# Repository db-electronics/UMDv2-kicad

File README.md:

# UMDv2
The Universal Mega Dumper v2 project aims to be a complete open-sourced solution for cartridge dumping and writing. It includes a very performant MCU which has a direct memory connection to a generalized databus consisting of 24 address bits and 16 data lines. Along with a dozen or so control signals, it should be sufficient to interface with most cartridge types.

## Cartridge Adapters
The UMDv2 by itself only includes a generalized connector with all its interfacing signals. Cartridge adapters must be used in order to interface to the physical media. All cartridge adapters, as they are created, are added to this project as submodules and will be linked in the CartAdapters directory.

### Cartridge Adapter ID
Each cartridge adapter has an MCP23008 on the I2C bus which identifies the console type for the adapter and thus prevents contention on IO.

* 0x00: no adapter
* 0x01: Sega Genesis 
* 0x02: Sega Master System

# Dependencies
## Parts Libraries
All components in this project depend on my KiCad libraries which are available at https://github.com/db-electronics/kicadlib . I don't use any pre-existing libraries - fight me.

## Firmware
There are two firmware components associated with this PCB: the STM32 fimware and the PC-side client. Both are available here:

* https://github.com/db-electronics/UMDv2-stm32
* https://github.com/db-electronics/UMDv2-python

Please note that version 2.0 is in its absolute infancy, don't expect to find any working releases in the firmware links above for the time being. The links are for provided provideness for completeness of documentation.

# Releases
## 2.0
https://oshpark.com/shared_projects/2dKXBoCG

The PCB version 2.0 release files are available in the releases section https://github.com/db-electronics/UMDv2-kicad/releases. Please note that this PCB is as of yet untested. Build at your own risk. I will post updates when I have begun testing this latest release.

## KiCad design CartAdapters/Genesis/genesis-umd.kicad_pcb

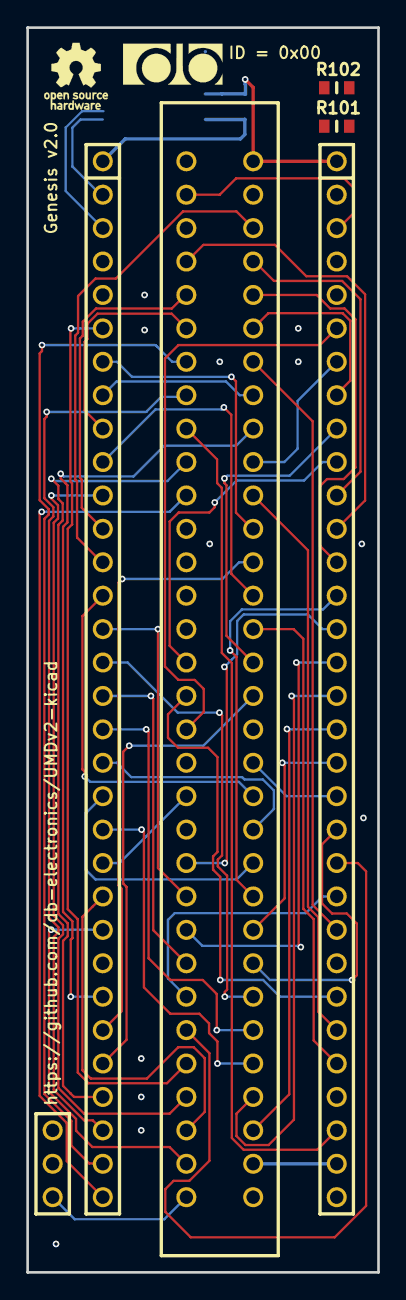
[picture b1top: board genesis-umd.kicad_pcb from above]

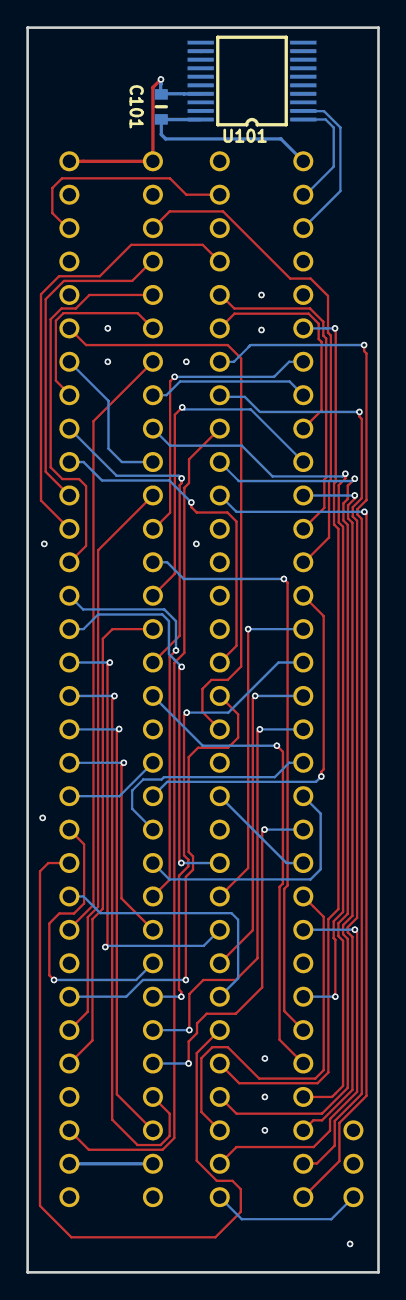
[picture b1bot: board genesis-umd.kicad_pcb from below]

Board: 2 copper layers, 26.7 x 94.6 mm, 6 parts (2 on the bottom side), 58 nets.

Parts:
C101: 0.1uF/50V; 0603
CON101: UMDv2-CONN; UMD-CONN-DIP64
CON102: GENESIS-CONN
R101, R102: 0; 0603
U101: MCP23008T-E_SS; SSOP-20

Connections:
+3V3: C101.1, CON101.1, U101.20
/5V_0: CON101.63, R101.2
/5V_1: CON101.34, CON102.A31
/A1: CON101.28, CON102.A17
/A2: CON101.37, CON102.A15
/A3: CON101.27, CON102.A13
/A4: CON101.38, CON102.A11
/A5: CON101.26, CON102.A9
/A6: CON101.41, CON102.A7
/A7: CON101.52, CON102.A5
/A8: CON101.13, CON102.A3
/A9: CON101.53, CON102.B4
/A10: CON101.12, CON102.B5
/A11: CON101.54, CON102.A4
/A12: CON101.57, CON102.A6
/A13: CON101.8, CON102.A8
/A14: CON101.58, CON102.A10
/A15: CON101.7, CON102.A12
/A16: CON101.10, CON102.A14
/A17: CON101.56, CON102.A16
/A18: CON101.9, CON102.B6
/A19: CON101.31, CON102.B7
/A20: CON101.30, CON102.B8
/A21: CON101.35, CON102.B9
/A22: CON101.29, CON102.B10
/A23: CON101.32, CON102.B11
/D0: CON101.14, CON102.A20
/D1: CON101.51, CON102.A23
/D2: CON101.16, CON102.A26
/D3: CON101.48, CON102.A29
/D4: CON101.21, CON102.A28
/D5: CON101.44, CON102.A25
/D6: CON101.20, CON102.A22
/D7: CON101.45, CON102.A19
/D8: CON101.19, CON102.A21
/D9: CON101.46, CON102.A24
/D10: CON101.18, CON102.A27
/D11: CON101.47, CON102.A30
/D12: CON101.17, CON102.B25
/D13: CON101.49, CON102.B24
/D14: CON101.15, CON102.B23
/D15: CON101.50, CON102.B22
/SCL: CON101.2, U101.1
/SDA: CON101.3, U101.2
/~ASEL~: CON101.42, CON102.B26
/~AS~: CON101.59, CON102.B18
/~CART~: CON101.67, CON102.B32
/~CE~: CON101.39, CON102.B17
/~DTACK~: CON101.22, CON102.B20
/~LWR~: CON101.6, CON102.B28
/~M3~: CON101.23, CON102.B30
/~MRES~: CON101.62, CON102.B2
/~RD~: CON101.55, CON102.B16
/~TIME~: CON101.24, CON102.B31
/~VRES~: CON101.43, CON102.B27
/~WR~: CON101.11, CON102.B29, R102.2
GND: C101.2, CON101.33, CON101.64, CON102.A1, CON102.A18, CON102.A32, U101.3, U101.4, U101.5, U101.6, U101.8, U101.9, U101.12, U101.13, U101.14, U101.15, U101.16, U101.17, U101.18, U101.19
unnamed: CON102.A2, R101.1, R102.1

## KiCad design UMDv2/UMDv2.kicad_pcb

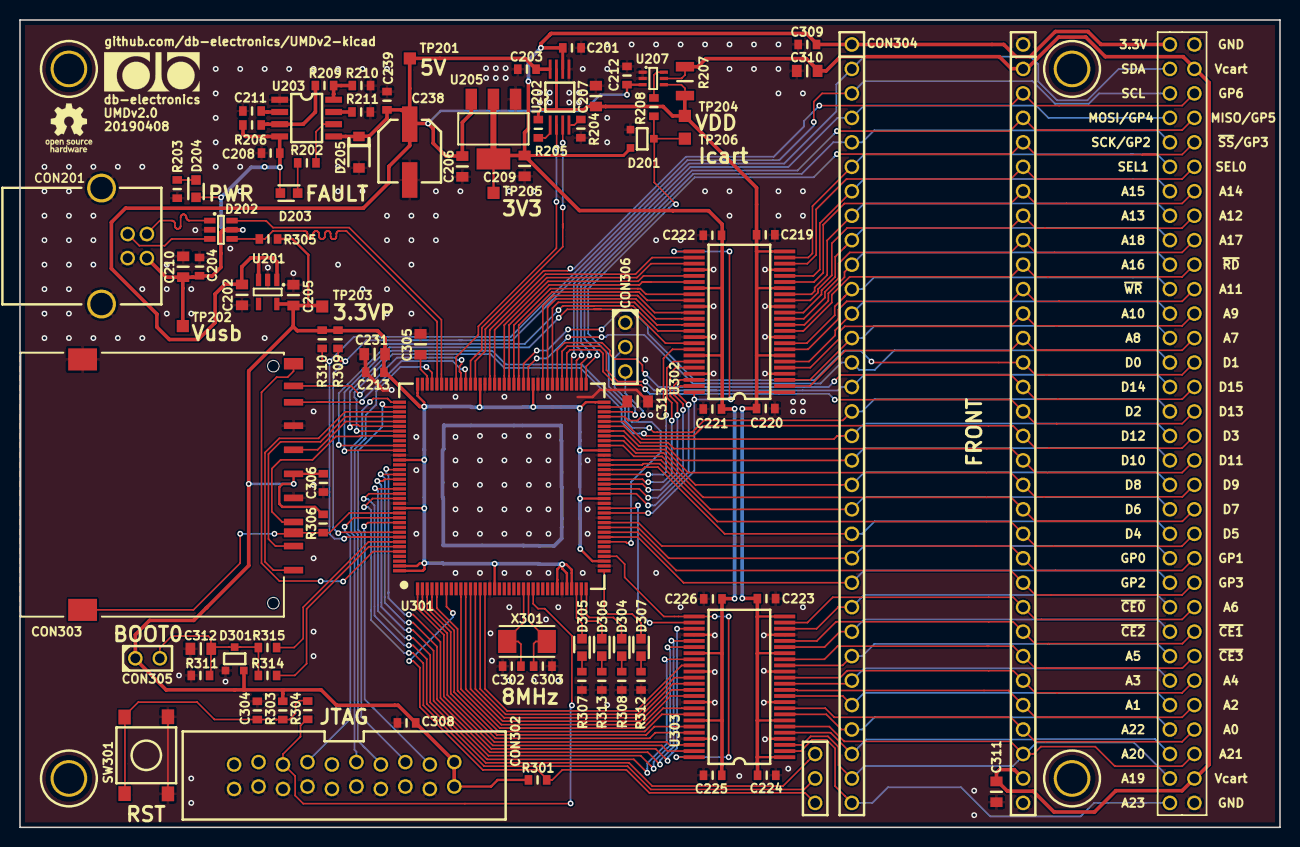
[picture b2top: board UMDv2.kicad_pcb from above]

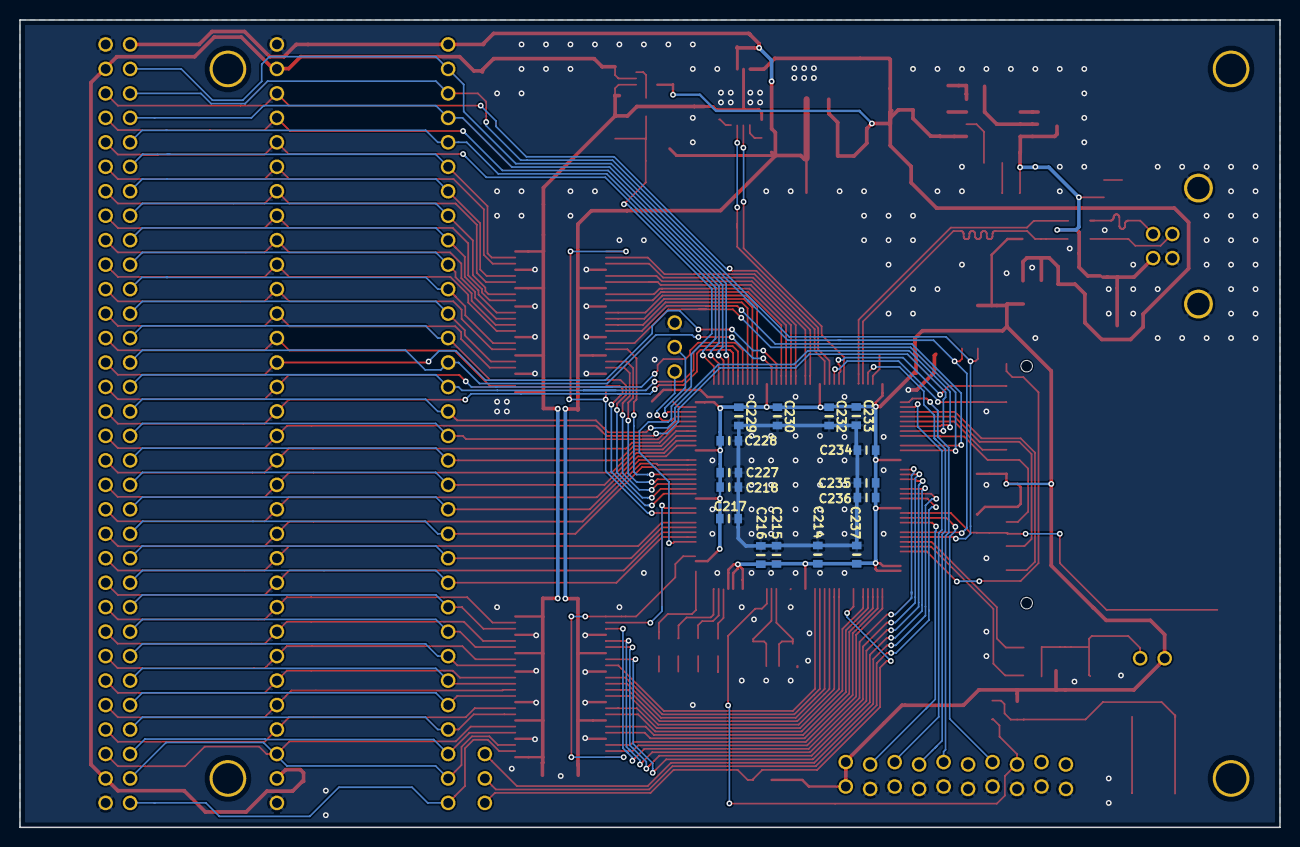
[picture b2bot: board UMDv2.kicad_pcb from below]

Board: 2 copper layers, 130.8 x 83.8 mm, 112 parts (15 on the bottom side), 152 nets.

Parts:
C201, C203, C204, C208, C212, C213, C214, C215, C216, C217, C218, C219, C220, C221, C222, C223, C224, C225, C226, C227, C228, C229, C230, C232, C233, C234, C235, C236, C237, C239, C304, C306, C308, C309: 0.1uF/50V; 0603
C202, C205, C206, C207, C209, C310, C311, C312: 10uF/16V; 0805
C210: 1uF/16V; 0805
C211: 1nF/50V; 0603
C231: 4.7uF/10V; 0805
C238: 22uF/50V; SMD-6.6x6.6
C302, C303: 18pF/10V; 0603
C305, C313: 2.2uF/10V; 0805
CON201: USB-B1HSB6; USB-B1HSxx
CON302: JTAG-2X10-HDR; HDR2X10-JTAG-SHROUD
CON303: 101-00405-75; SDCARD-AMP-10100405
CON304: UMDv2-CONN; UMD-CONN-DIP64-2
CON305: HDR1X2
CON306: HDR1X3
D201, D301: BAT54S; SOT23
D202: USBLC6-2SC6; SOT-23-6
D203, D204: LG_M67K-G1J2-24-Z; SMD-2
D205: BZT52-B5V6J; SOD123
D304, D305, D306, D307: LO_M67K-K2M1-24-Z; SMD-2
MEC101, MEC102, MEC103, MEC104: NSP-4-6-01; 4-40-SCREW
R202, R203, R307, R308, R312, R313: 750; 0603
R204: 1.20k; 0603
R205, R303, R306: 10.0k; 0603
R206: 118k; 0603
R207: 0.1; 1206
R208: 100; 0603
R209: 7.50k; 0603
R210, R211: 43.2k; 0603
R301, R309, R310: 2.20k; 0603
R304, R314, R315: 470; 0603
R305: 1.50k; 0603
R311: 220k; 0603
SW301: PTS645SM43SMTR92_LFS; PTS645
TP201, TP202, TP203, TP204, TP205, TP206: TP_50; TP50
U201: MIC5504-3.3YM5-TR; SC-74A
U202: TPS2115APWR; TSSOP-8_4.4mm
U203: TPS25921ADR; SOIC-8-3.9MM
U205: AZ1117CH-3.3TRG1; SOT-223
U207: INA199A2DCKR; SOT-363
U301: STM32F413ZHT6; LQFP-144
U302, U303: 74ALVC164245DL,118; BSSOP-48-7.50mm
X301: ECS-80-18-30-JGN-TR; ECX-53
logo101: db Electronics Logo; db-logo_10mm
logo102: OSHW Logo; oshw-logo_5mm

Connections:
+3.3VP: C205.1, C213.2, C214.2, C215.2, C216.2, C217.2, C218.2, C227.2, C228.2, C229.2, C230.2, C231.1, C232.2, C233.2, C234.2, C235.2, C236.2, C237.2, C306.2, C308.2, CON302.1, CON302.2, CON303.4, CON305.1, D301.2, R301.1, R303.2, R305.1, R306.1, R309.1, R310.1, TP203.1, U201.5, U301.17, U301.30, U301.32, U301.33, U301.39, U301.52, U301.62, U301.72, U301.84, U301.95, U301.108, U301.121, U301.131, U301.143, U301.144
+3V3: C201.2, C209.1, C221.2, C222.2, C225.2, C226.2, C309.2, CON304.1, D201.2, TP205.1, U202.6, U205.2, U302.31, U302.42, U303.31, U303.42
+5V: C202.1, C203.2, C206.1, C212.2, C238.1, C239.2, D205.1, TP201.1, U201.1, U201.3, U202.8, U203.5, U205.3, U207.3
/Microcontroller/A0: U301.10, U303.40
/Microcontroller/A1: U301.11, U303.38
/Microcontroller/A2: U301.12, U303.37
/Microcontroller/A3: U301.13, U303.36
/Microcontroller/A4: U301.14, U303.35
/Microcontroller/A5: U301.15, U303.33
/Microcontroller/A6: U301.50, U303.26
/Microcontroller/A7: U301.53, U302.47
/Microcontroller/A8: U301.54, U302.46
/Microcontroller/A9: U301.55, U302.44
/Microcontroller/A10: U301.56, U302.43
/Microcontroller/A11: U301.57, U302.41
/Microcontroller/A12: U301.87, U302.33
/Microcontroller/A13: U301.88, U302.32
/Microcontroller/A14: U301.89, U302.30
/Microcontroller/A15: U301.90, U302.29
/Microcontroller/A16: U301.80, U302.37
/Microcontroller/A17: U301.81, U302.36
/Microcontroller/A18: U301.82, U302.35
/Microcontroller/A19: U301.2, U303.46
/Microcontroller/A20: U301.3, U303.44
/Microcontroller/A21: U301.4, U303.43
/Microcontroller/A22: U301.5, U303.41
/Microcontroller/A23: U301.1, U303.47
/Microcontroller/A24: CON304.65, U301.128
/Microcontroller/A25: CON304.66, U301.129
/Microcontroller/BOOT0: C312.1, CON305.2, D301.3, R311.2, R314.1, R315.2
/Microcontroller/BOOT_EN: R314.2, U301.139
/Microcontroller/D0: CON304.14, U301.85
/Microcontroller/D1: CON304.51, U301.86
/Microcontroller/D2: CON304.16, U301.114
/Microcontroller/D3: CON304.48, U301.115
/Microcontroller/D4: CON304.21, U301.58
/Microcontroller/D5: CON304.44, U301.59
/Microcontroller/D6: CON304.20, U301.60
/Microcontroller/D7: CON304.45, U301.63
/Microcontroller/D8: CON304.19, U301.64
/Microcontroller/D9: CON304.46, U301.65
/Microcontroller/D10: CON304.18, U301.66
/Microcontroller/D11: CON304.47, U301.67
/Microcontroller/D12: CON304.17, U301.68
/Microcontroller/D13: CON304.49, U301.77
/Microcontroller/D14: CON304.15, U301.78
/Microcontroller/D15: CON304.50, U301.79
/Microcontroller/D+: D202.4, R305.2, U301.104
/Microcontroller/D-: D202.6, U301.103
/Microcontroller/GP0: CON304.22, U301.46
/Microcontroller/GP1: CON304.43, U301.47
/Microcontroller/GP2: CON304.23, U301.44
/Microcontroller/GP3: CON304.42, U301.45
/Microcontroller/GP8: CON304.62, U301.96
/Microcontroller/Icart: D201.3, R208.2, TP206.1, U301.43
/Microcontroller/JRST: CON302.3, U301.134
/Microcontroller/JTCK: CON302.9, U301.109
/Microcontroller/JTDI: CON302.5, U301.110
/Microcontroller/JTDO: CON302.13, U301.133
/Microcontroller/JTMS: CON302.7, U301.105
/Microcontroller/LED0: D307.2, U301.37
/Microcontroller/LED1: D304.2, U301.36
/Microcontroller/LED2: D306.2, U301.35
/Microcontroller/LED3: D305.2, U301.34
/Microcontroller/SCL1: CON304.2, R309.2, U301.136
/Microcontroller/SDA1: CON304.3, R310.2, U301.137
/Microcontroller/SDIO_CK: CON303.5, U301.113
/Microcontroller/SDIO_CMD: CON303.2, U301.116
/Microcontroller/SDIO_D0: CON303.7, U301.98
/Microcontroller/SDIO_D1: CON303.8, U301.99
/Microcontroller/SDIO_D2: CON303.9, U301.111
/Microcontroller/SDIO_D3: CON303.1, U301.112
/Microcontroller/SEL0: U301.92, U302.27
/Microcontroller/SEL1: U301.93, U302.26
/Microcontroller/SPI2_MISO: CON304.61, U301.75
/Microcontroller/SPI2_MOSI: CON304.4, U301.76
/Microcontroller/SPI2_NSS: CON304.60, U301.73
/Microcontroller/SPI2_SCK: CON304.5, U301.74
/Microcontroller/UA0: CON304.36, U303.9
/Microcontroller/UA1: CON304.28, U303.11
/Microcontroller/UA2: CON304.37, U303.12
/Microcontroller/UA3: CON304.27, U303.13
/Microcontroller/UA4: CON304.38, U303.14
/Microcontroller/UA5: CON304.26, U303.16
/Microcontroller/UA6: CON304.41, U303.23
/Microcontroller/UA7: CON304.52, U302.2
/Microcontroller/UA8: CON304.13, U302.3
/Microcontroller/UA9: CON304.53, U302.5
/Microcontroller/UA10: CON304.12, U302.6
/Microcontroller/UA11: CON304.54, U302.8
/Microcontroller/UA12: CON304.57, U302.16
/Microcontroller/UA13: CON304.8, U302.17
/Microcontroller/UA14: CON304.58, U302.19
/Microcontroller/UA15: CON304.7, U302.20
/Microcontroller/UA16: CON304.10, U302.12
/Microcontroller/UA17: CON304.56, U302.13
/Microcontroller/UA18: CON304.9, U302.14
/Microcontroller/UA19: CON304.31, U303.3
/Microcontroller/UA20: CON304.30, U303.5
/Microcontroller/UA21: CON304.35, U303.6
/Microcontroller/UA22: CON304.29, U303.8
/Microcontroller/UA23: CON304.32, U303.2
/Microcontroller/USART3_RX: CON306.2, U301.70
/Microcontroller/USART3_TX: CON306.3, U301.69
/Microcontroller/USEL0: CON304.59, U302.22
/Microcontroller/USEL1: CON304.6, U302.23
/Microcontroller/VSEL0: U202.2, U301.100
/Microcontroller/VSEL1: U202.3, U301.97
/Microcontroller/~CE0~: U301.123, U303.27
/Microcontroller/~CE1~: U301.124, U303.29
/Microcontroller/~CE2~: U301.125, U303.30
/Microcontroller/~CE3~: U301.127, U303.32
/Microcontroller/~DTCT~: CON304.67, R301.2, U301.7
/Microcontroller/~OUT_EN0~: U301.40, U303.25, U303.48
/Microcontroller/~OUT_EN1~: U301.49, U302.25, U302.48
/Microcontroller/~RD~: U301.118, U302.38
/Microcontroller/~RST: CON302.15, R304.1, U301.25
/Microcontroller/~SDCD~: CON303.10, R306.2, U301.132
/Microcontroller/~SDWP~: CON303.11, U301.140
/Microcontroller/~UCE0~: CON304.24, U303.22
/Microcontroller/~UCE1~: CON304.40, U303.20
/Microcontroller/~UCE2~: CON304.25, U303.19
/Microcontroller/~UCE3~: CON304.39, U303.17
/Microcontroller/~URD~: CON304.55, U302.11
/Microcontroller/~UWR~: CON304.11, U302.9
/Microcontroller/~WR~: U301.119, U302.40
/Power Section/Din+: CON201.3, D202.3
/Power Section/Din-: CON201.2, D202.1
GND: C201.1, C202.2, C203.1, C204.2, C205.2, C206.2, C207.2, C208.1, C209.2, C210.2, C211.1, C212.1, C213.1, C214.1, C215.1, C216.1, C217.1, C218.1, C219.1, C220.1, C221.1, C222.1, C223.1, C224.1, C225.1, C226.1, C227.1, C228.1, C229.1, C230.1, C231.2, C232.1, C233.1, C234.1, C235.1, C236.1, C237.1, C238.2, C239.1, C302.2, C303.2, C304.2, C305.2, C306.1, C308.1, C309.1, C310.1, C311.2, C312.2, C313.2, CON201.4, CON201.5, CON302.4, CON302.6, CON302.8, CON302.10, CON302.12, CON302.14, CON302.16, CON302.18, CON302.20, CON303.3, CON303.6, CON303.12, CON304.33, CON304.64, CON306.1, D201.1, D202.2, D205.2, D301.1, R203.2, R204.1, R210.1, R211.1, R307.1, R308.1, R311.1, R312.1, R313.1, SW301.3, SW301.4, U201.2, U202.5, U203.1, U205.1, U207.1, U207.2, U301.16, U301.31, U301.38, U301.48, U301.51, U301.61, U301.83, U301.94, U301.107, U301.120, U301.130, U302.4, U302.10, U302.15, U302.21, U302.28, U302.34, U302.39, U302.45, U303.4, U303.10, U303.15, U303.21, U303.28, U303.34, U303.39, U303.45
unnamed: C211.2, U203.2
unnamed: C302.1, U301.23, X301.2
unnamed: C303.1, U301.24, X301.1
unnamed: C304.1, R303.1, R304.2, SW301.1, SW301.2
unnamed: C305.1, U301.106
unnamed: C313.1, U301.71
unnamed: D203.1, R202.2
unnamed: D204.1, R203.1
unnamed: D304.1, R308.2
unnamed: D305.1, R307.2
unnamed: D306.1, R313.2
unnamed: D307.1, R312.2
unnamed: R202.1, U203.6
unnamed: R204.2, U202.4
unnamed: R205.1, U202.1
unnamed: R206.2, R209.1, U203.3
unnamed: R208.1, U207.6
unnamed: R209.2, R210.2, U203.8
unnamed: R211.2, U203.7
unnamed: R315.1, U301.138
VDD: C207.1, C219.2, C220.2, C223.2, C224.2, R205.2, R207.2, TP204.1, U202.7, U207.4, U302.1, U302.7, U302.18, U302.24, U303.1, U303.7, U303.18, U303.24
Vcart: C310.2, C311.1, CON304.34, CON304.63, R207.1, U207.5
Vusb: C204.1, C208.2, C210.1, CON201.1, D202.5, D203.2, D204.2, R206.1, TP202.1, U203.4

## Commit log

2018-09-07 initial project commit
2018-09-07 working on schematic
2018-09-08 added SD card connector
2018-09-09 working on schematic, added some parts to PCB
2018-09-09 added USB ESD diode
2018-09-09 working on schematic, how many commit msgs can I come up with?
2018-09-10 alternate USB power input
2018-09-10 changed load switches because Ste is always right
2018-09-11 added current sense amp
2018-09-11 new schematic sheet for power section
2018-09-12 added microcontroller sheet to schematic
2018-09-13 added component for sense resistor
2018-09-14 consistent global pins throughout
2018-09-16 added reset circuitry
2018-09-17 added serial flash
2018-09-18 re-annotated schematic with new sheet numbers, placed all current components on PCB
2018-09-18 added first board outline
2018-09-18 minor changes
2018-09-21 added 4x20 LCD symbol to schematic
2018-10-11 added new hierarchical sheet for user interface
2018-10-16 migrated to KiCad v5
2018-11-06 component placement, bypass caps
2018-11-06 more component placement
2018-11-07 ajsfasfasfkihjasd;fkj
2018-11-07 lots of parts placement
2018-11-08 routing the power supply section
2018-11-08 bit of work
2018-11-09 just routing
2018-11-09 routing
2018-11-09 playing with diff routing on USB
2018-11-11 routing some PCB
2018-11-12 1-2-1-2 patate poil maudit cave mian nana nana
2018-11-12 power routing
2019-01-09 switched to STM32F407 mcu
2019-01-10 changed USB lines
2019-01-11 modifying the sch for STM32F407
2019-01-14 new pinout on UMDv2 conn
2019-01-15 working on schematic/
2019-01-15 these git commit messages suck, I'm sorry
2019-01-16 component placement
2019-01-17 routing power beneath MCU
2019-01-17 routing the PCB
2019-01-18 more routing
2019-01-22 lots of routing work
2019-01-24 the time they are a-routing
2019-01-29 just a-routing
2019-02-07 added 1.5k pullep to USB D+
2019-02-13 changed MCU to STM32F413
2019-02-13 fixed pinout issues from MCU change
2019-02-13 re-routing for QSPI
2019-02-19 removed dual USB, still need an eFUSE
2019-02-20 added eFuse to USB input, remove redundant Vdd load switch
2019-02-22 started parts placement with new power section
2019-02-22 better power supply caps
2019-02-22 added note about capacitor on Boot0
2019-02-25 added software control of Boot0 in schematic
2019-02-27 changed signal names to VSEL0/1, added schottky diode to BOOT0 circuit
2019-02-28 power supply placement and routing
2019-03-01 removed QSPI flash and USR_BTN because they won't be necessary
2019-03-01 added calculations spreadsheet for efuse
2019-03-02 improved USB and power routing, added 2 more user LEDs
2019-03-02 added new UMD-CONN with testpoints and 4-40 screws
2019-03-04 added logos
2019-03-07 minor changes to PCB
2019-03-13 finished LA connector, started review
2019-03-14 added adapter-genesis project files
2019-03-14 working on GND planes
2019-03-14 better organization for cart adapters
2019-03-15 working on Genesis cart adapter sch
2019-03-24 connected all signals for genesis adpater
2019-03-25 not sure what I changed
2019-03-29 updated UMDv2 symbol and footprint, changed AN0-AN1 to A24, A25
2019-03-30 working
2019-04-01 optimizing signals, re-arranged A24/A25 and several GPx on UMDv2 connector
2019-04-01 genesis cart adapter work
2019-04-03 increased spacing on UMDv2 connector
2019-04-03 bit of routing on genesis adapter
2019-04-05 added board dimensions to dwgs layer
2019-04-08 pulling the trigger on v2.0 PCB release
2019-04-25 bit of routing the on Genesis Adapter
2019-04-25 proper nCART wiring for Genesis adapter
2019-04-26 prelim routing complete on genesis adapter
2019-05-07 ground plane added to genesis UMD adapter
2020-02-10 changed Genesis CE to CE3
2020-02-10 added 0 jumpers for nWR pin selection to support legacy Bitmap Bureau PCBs
2020-02-11 moved Genesis adpater to its own repo as a submodule of main UMDv2 project
2020-02-11 I think I understand submodules
2020-02-12 updated OSHPark link in README
2020-02-14 BOM change on Genesis cartridge adapter
2020-03-14 added sms cartridge adapter
2020-03-16 updated readme with valid cartridge adapter IDs
2020-03-16 missed a commit on Genesis adapter sudmodule
2020-03-21 updating for sms and gen adapter pcb releases
2021-06-05 rescued symbols

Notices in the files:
CartAdapters/Genesis/genesis-umd.kicad_pcb:
Licensed Under CERN OHL v.1.2
UMDv2/UMDv2.kicad_pcb:
Copyright René Richard 2019
